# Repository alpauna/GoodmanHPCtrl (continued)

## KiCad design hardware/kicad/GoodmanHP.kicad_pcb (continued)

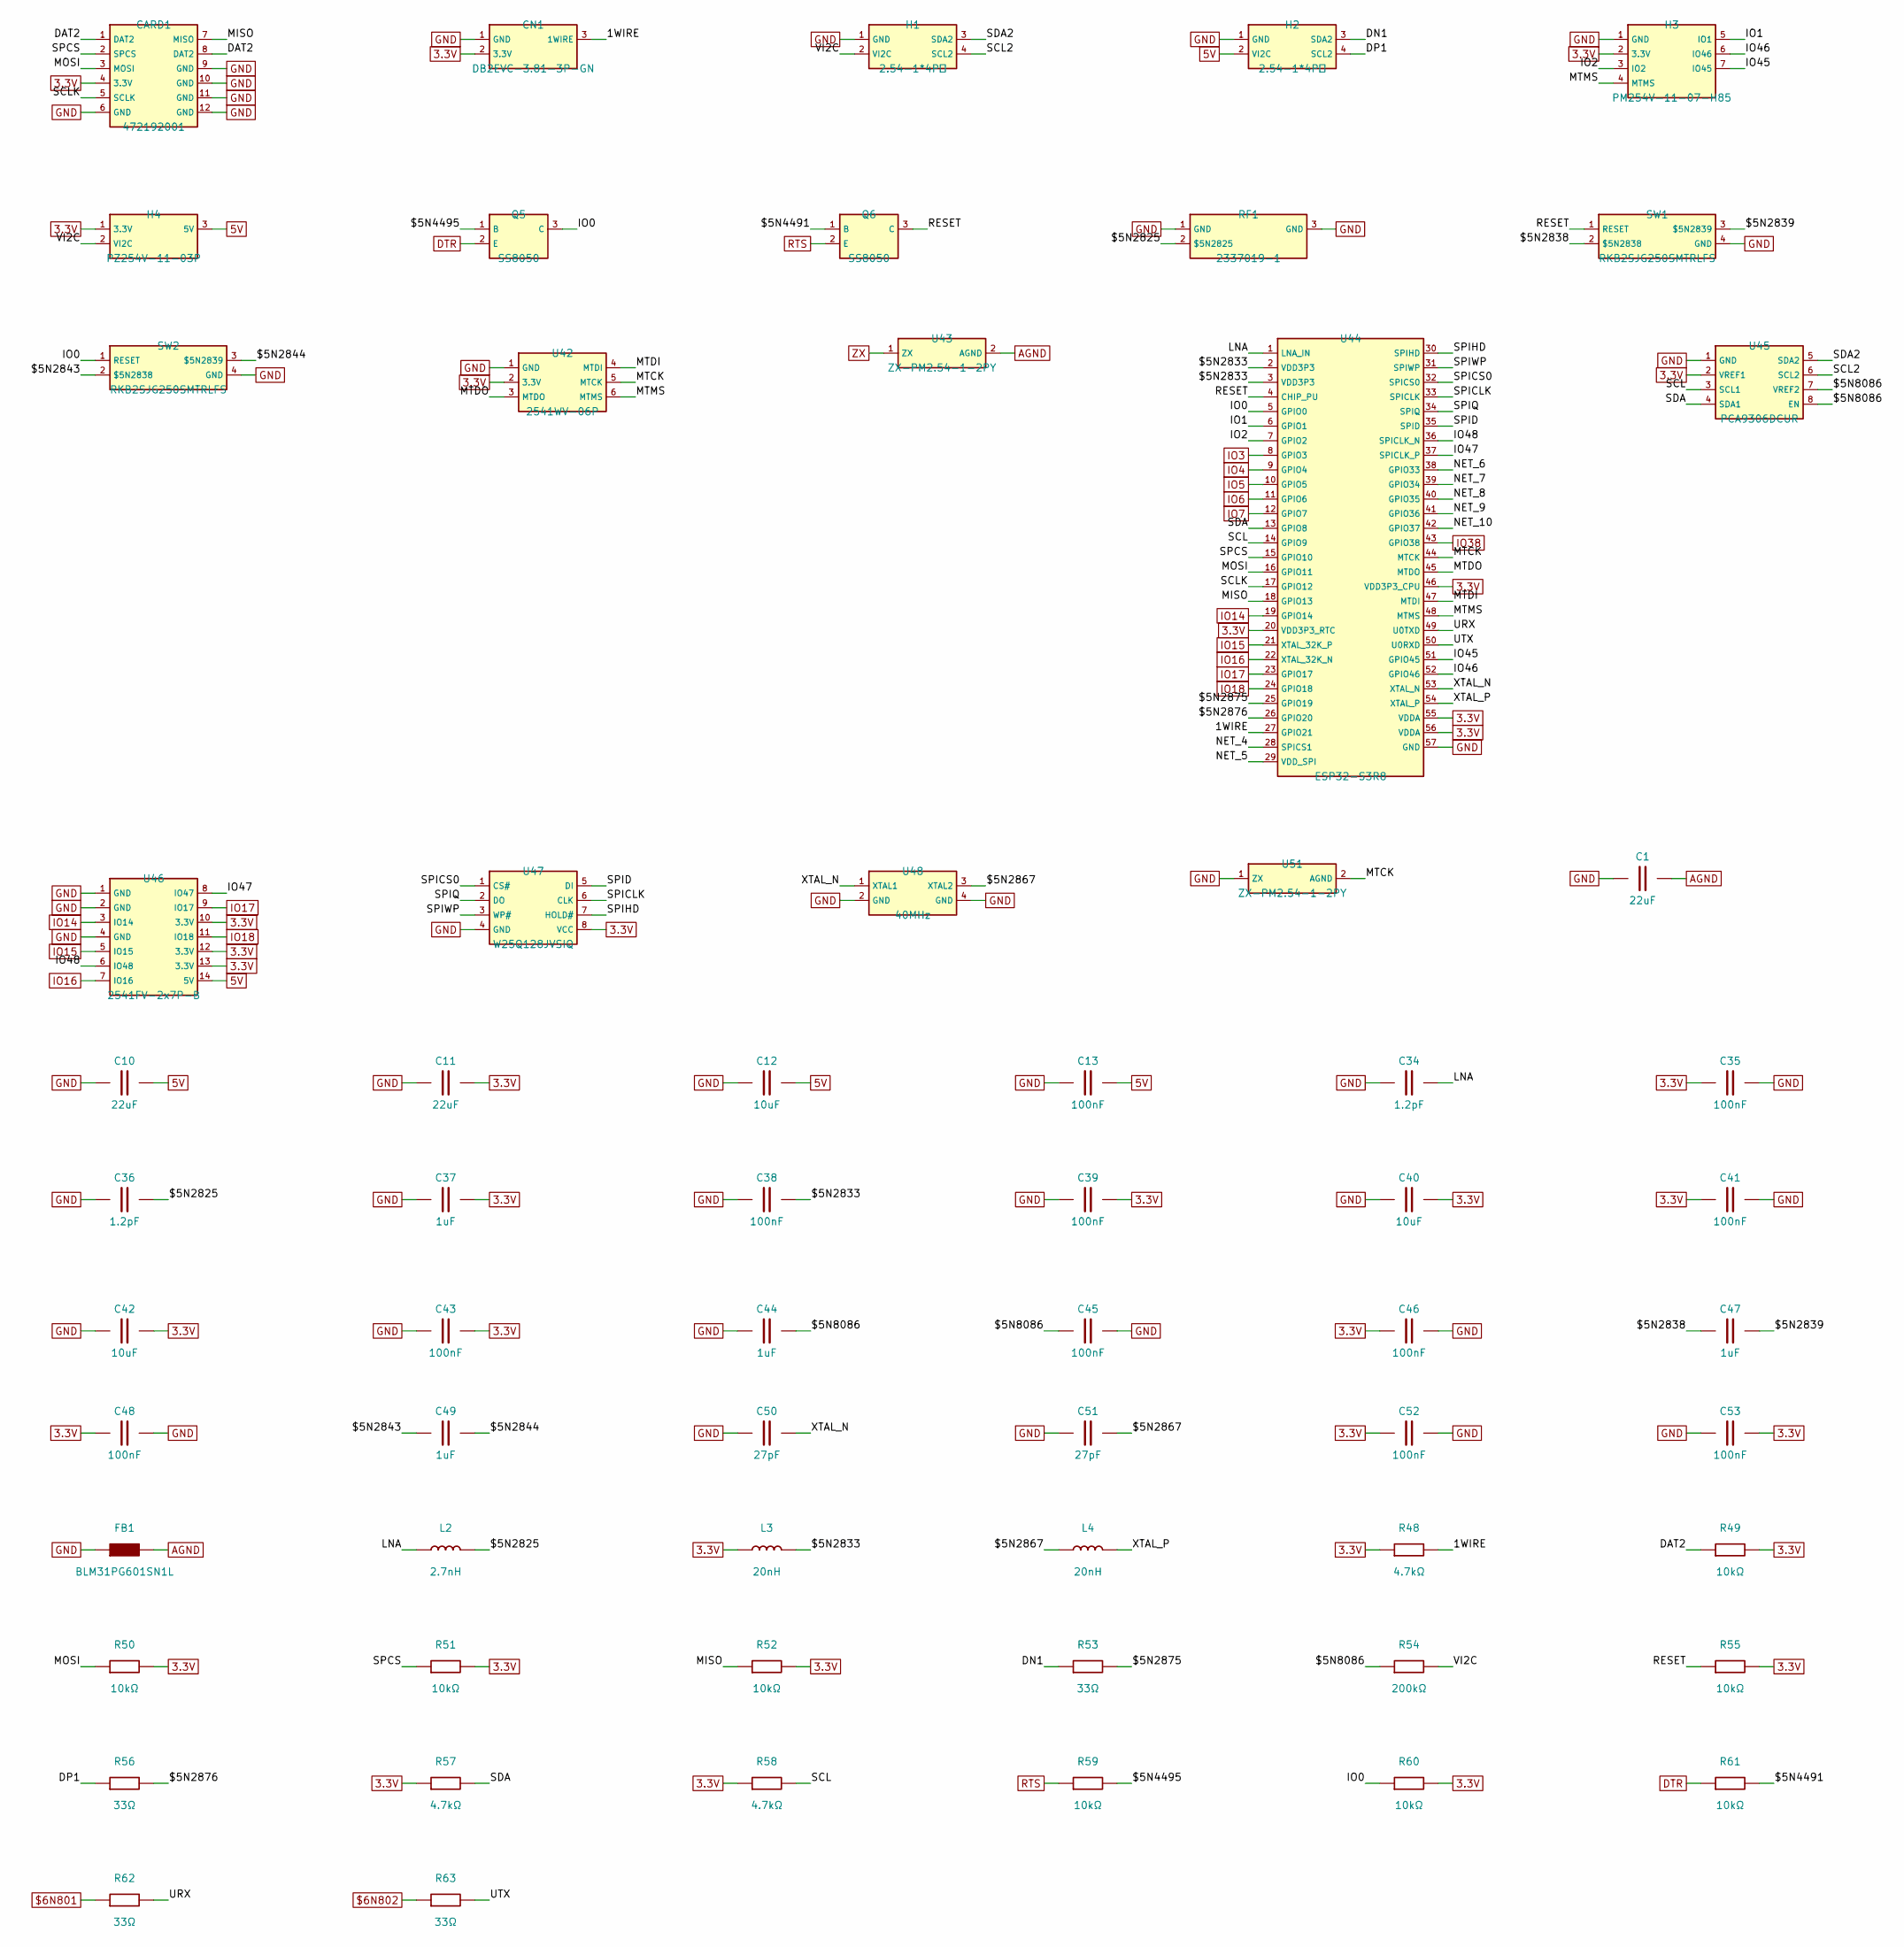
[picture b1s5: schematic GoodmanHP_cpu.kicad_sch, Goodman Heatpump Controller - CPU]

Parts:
C1: 22uF; C1812; LCSC C22388553
C10, C11: 22uF; C0805; LCSC C907991
C12, C40, C42: 10uF; C0402; LCSC C15525
C13, C35, C38, C39, C41, C43, C45, C46, C48, C52, C53: 100nF; C0201; LCSC C85923
C34, C36: 1.2pF; C0201; LCSC C85895
C37, C44, C47, C49: 1uF; C0201; LCSC C76929
C50, C51: 27pF; C0201; LCSC C384976
CARD1: 472192001; TF-SMD_472192001; LCSC C164170
CN1: DB2EVC-3.81-3P-GN; CONN-TH_3P-P3.81_DB2EVC-3.81-3P; LCSC C395692
FB1: BLM31PG601SN1L; L1206; LCSC C16902
H1, H2: 2.54-1*4P母; HDR-TH_4P-P2.54-V-F; LCSC C2718488
H3: PM254V-11-07-H85; HDR-TH_7P-P2.54-V-F; LCSC C2832270
H4: PZ254V-11-03P; HDR-TH_3P-P2.54-V-M_PZ254V-11-03P; LCSC C2937625
L2: 2.7nH; L0201; LCSC C7216765
L3, L4: 20nH; IND-SMD_L1.2-W0.6-1; LCSC C330860
Q5, Q6: SS8050; SOT-23-3_L2.9-W1.3-P1.90-LS2.4-BR; LCSC C916392
R48, R57, R58: 4.7kΩ; R0201; LCSC C138135
R49, R50, R51, R52, R55, R59, R60, R61: 10kΩ; R0201; LCSC C473048
R53, R56, R62, R63: 33Ω; R0201; LCSC C423356
R54: 200kΩ; R0201; LCSC C138163
RF1: 2337019-1; ANT-SMD_2337019-1; LCSC C434807
SW1, SW2: RKB2SJG250SMTRLFS; SW-SMD_4P-L4.2-W3.2-P2.15-LS4.6; LCSC C2927788
U42: 2541WV-06P; HDR-TH_6P-P2.54-V-M; LCSC C5383115
U43, U51: ZX-PM2.54-1-2PY; HDR-TH_2P-P2.54-V-F; LCSC C7499322
U44: ESP32-S3R8; QFN-56_L7.0-W7.0-P0.40-TL-EP4.0; LCSC C2913194
U45: PCA9306DCUR; SSOP-8_L2.0-W2.3-P0.50-LS3.1-BR; LCSC C33196
U46: 2541FV-2x7P-B; HDR-TH_2541FV-2X7P-B; LCSC C25503125
U47: W25Q128JVSIQ; SOIC-8_L5.3-W5.3-P1.27-LS8.0-BL; LCSC C113767
U48: 40MHz; CRYSTAL-SMD_4P-L2.0-W1.6-BL; LCSC C42464327

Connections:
1WIRE: CN1.3 (1WIRE), R48.2, U44.27 (GPIO21)
3.3V: C11.2, C35.1, C37.2, C39.2, C40.2, C41.1, C42.2, C43.2, C46.1, C48.1, C52.1, C53.2, CARD1.4 (3.3V), CN1.2 (3.3V), H3.2 (3.3V), H4.1 (3.3V), L3.1, R48.1, R49.2, R50.2, R51.2, R52.2, R55.2, R57.1, R58.1, R60.2, U42.2 (3.3V), U44.20 (VDD3P3_RTC), U44.46 (VDD3P3_CPU), U44.55 (VDDA), U44.56 (VDDA), U45.2 (VREF1), U46.10 (3.3V), U46.12 (3.3V), U46.13 (3.3V), U47.8 (VCC); also elsewhere on the board
5V: C10.2, C12.2, C13.2, H2.2 (VI2C), H4.3 (5V), U46.14 (5V); also elsewhere on the board
$5N2825: C36.2, L2.2, RF1.2 ($5N2825)
$5N2833: C38.2, L3.2, U44.2 (VDD3P3), U44.3 (VDD3P3)
$5N2838: C47.1, SW1.2 ($5N2838)
$5N2839: C47.2, SW1.3 ($5N2839)
$5N2843: C49.1, SW2.2 ($5N2838)
$5N2844: C49.2, SW2.3 ($5N2839)
$5N2867: C51.2, L4.1, U48.3 (XTAL2)
$5N2875: R53.2, U44.25 (GPIO19)
$5N2876: R56.2, U44.26 (GPIO20)
$5N4491: Q6.1 (B), R61.2
$5N4495: Q5.1 (B), R59.2
$5N8086: C44.2, C45.1, R54.1, U45.7 (VREF2), U45.8 (EN)
$6N801: R62.1; also elsewhere on the board
$6N802: R63.1; also elsewhere on the board
AGND: C1.2, FB1.2, U43.2 (AGND); also elsewhere on the board
DAT2: CARD1.1 (DAT2), CARD1.8 (DAT2), R49.1
DN1: H2.3 (SDA2), R53.1
DP1: H2.4 (SCL2), R56.1
DTR: Q5.2 (E), R61.1; also elsewhere on the board
GND: C1.1, C10.1, C11.1, C12.1, C13.1, C34.1, C35.2, C36.1, C37.1, C38.1, C39.1, C40.1, C41.2, C42.1, C43.1, C44.1, C45.2, C46.2, C48.2, C50.1, C51.1, C52.2, C53.1, CARD1.6 (GND), CARD1.9 (GND), CARD1.10 (GND), CARD1.11 (GND), CARD1.12 (GND), CN1.1 (GND), FB1.1, H1.1 (GND), H2.1 (GND), H3.1 (GND), RF1.1 (GND), RF1.3 (GND), SW1.4 (GND), SW2.4 (GND), U42.1 (GND), U44.57 (GND), U45.1 (GND), U46.1 (GND), U46.2 (GND), U46.4 (GND), U47.4 (GND), U48.2 (GND), U48.4 (GND), U51.1 (ZX); also elsewhere on the board
IO0: Q5.3 (C), R60.1, SW2.1 (RESET), U44.5 (GPIO0)
IO1: H3.5 (IO1), U44.6 (GPIO1)
IO2: H3.3 (IO2), U44.7 (GPIO2)
IO3: U44.8 (GPIO3); also elsewhere on the board
IO4: U44.9 (GPIO4); also elsewhere on the board
IO5: U44.10 (GPIO5); also elsewhere on the board
IO6: U44.11 (GPIO6); also elsewhere on the board
IO7: U44.12 (GPIO7); also elsewhere on the board
IO14: U44.19 (GPIO14), U46.3 (IO14); also elsewhere on the board
IO15: U44.21 (XTAL_32K_P), U46.5 (IO15); also elsewhere on the board
IO16: U44.22 (XTAL_32K_N), U46.7 (IO16); also elsewhere on the board
IO17: U44.23 (GPIO17), U46.9 (IO17); also elsewhere on the board
IO18: U44.24 (GPIO18), U46.11 (IO18); also elsewhere on the board
IO38: U44.43 (GPIO38); also elsewhere on the board
IO45: H3.7 (IO45), U44.51 (GPIO45)
IO46: H3.6 (IO46), U44.52 (GPIO46)
IO47: U44.37 (SPICLK_P), U46.8 (IO47)
IO48: U44.36 (SPICLK_N), U46.6 (IO48)
LNA: C34.2, L2.1, U44.1 (LNA_IN)
MISO: CARD1.7 (MISO), R52.1, U44.18 (GPIO13)
MOSI: CARD1.3 (MOSI), R50.1, U44.16 (GPIO11)
MTCK: U42.5 (MTCK), U44.44 (MTCK), U51.2 (AGND)
MTDI: U42.4 (MTDI), U44.47 (MTDI)
MTDO: U42.3 (MTDO), U44.45 (MTDO)
MTMS: H3.4 (MTMS), U42.6 (MTMS), U44.48 (MTMS)
NET_4: U44.28 (SPICS1)
NET_5: U44.29 (VDD_SPI)
NET_6: U44.38 (GPIO33)
NET_7: U44.39 (GPIO34)
NET_8: U44.40 (GPIO35)
NET_9: U44.41 (GPIO36)
NET_10: U44.42 (GPIO37)
RESET: Q6.3 (C), R55.1, SW1.1 (RESET), U44.4 (CHIP_PU)
RTS: Q6.2 (E), R59.1; also elsewhere on the board
SCL: R58.2, U44.14 (GPIO9), U45.3 (SCL1)
SCL2: H1.4 (SCL2), U45.6 (SCL2)
SCLK: CARD1.5 (SCLK), U44.17 (GPIO12)
SDA: R57.2, U44.13 (GPIO8), U45.4 (SDA1)
SDA2: H1.3 (SDA2), U45.5 (SDA2)
SPCS: CARD1.2 (SPCS), R51.1, U44.15 (GPIO10)
SPICLK: U44.33 (SPICLK), U47.6 (CLK)
SPICS0: U44.32 (SPICS0), U47.1 (CS#)
SPID: U44.35 (SPID), U47.5 (DI)
SPIHD: U44.30 (SPIHD), U47.7 (HOLD#)
SPIQ: U44.34 (SPIQ), U47.2 (DO)
SPIWP: U44.31 (SPIWP), U47.3 (WP#)
URX: R62.2, U44.49 (U0TXD)
UTX: R63.2, U44.50 (U0RXD)
VI2C: H1.2 (VI2C), H4.2 (VI2C), R54.2
XTAL_N: C50.2, U44.53 (XTAL_N), U48.1 (XTAL1)
XTAL_P: L4.2, U44.54 (XTAL_P)
ZX: U43.1 (ZX); also elsewhere on the board

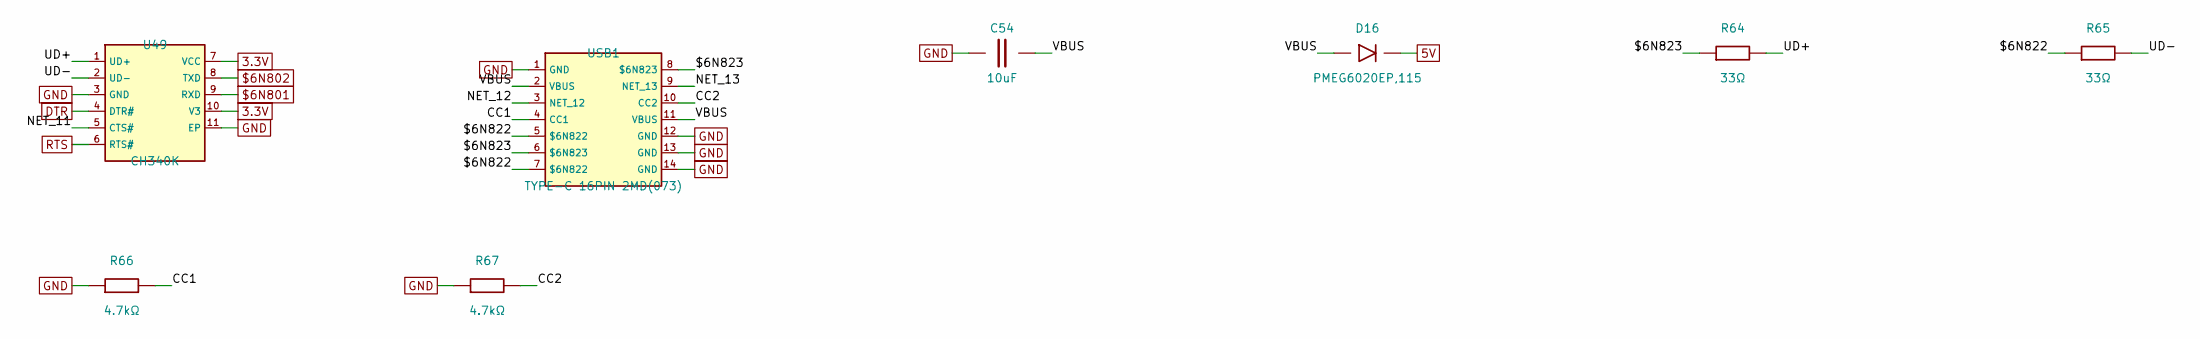
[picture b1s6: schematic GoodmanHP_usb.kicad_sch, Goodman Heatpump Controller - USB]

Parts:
C54: 10uF; C0402; LCSC C15525
D16: PMEG6020EP,115; SOD-128_L3.7-W2.5-LS4.7-FD; LCSC C179433
R64, R65: 33Ω; R0201; LCSC C423356
R66, R67: 4.7kΩ; R0201; LCSC C138135
U49: CH340K; ESOP-10_L4.9-W3.9-P1.00-LS6.2-BL-EP; LCSC C968586
USB1: TYPE-C 16PIN 2MD(073); USB-C-SMD_TYPE-C-6PIN-2MD-073; LCSC C2765186

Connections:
3.3V: U49.7 (VCC), U49.10 (V3); also elsewhere on the board
5V: D16.1 (K); also elsewhere on the board
$6N801: U49.9 (RXD); also elsewhere on the board
$6N802: U49.8 (TXD); also elsewhere on the board
$6N822: R65.1, USB1.5 ($6N822), USB1.7 ($6N822)
$6N823: R64.1, USB1.6 ($6N823), USB1.8 ($6N823)
CC1: R66.2, USB1.4 (CC1)
CC2: R67.2, USB1.10 (CC2)
DTR: U49.4 (DTR#); also elsewhere on the board
GND: C54.1, R66.1, R67.1, U49.3 (GND), U49.11 (EP), USB1.1 (GND), USB1.12 (GND), USB1.13 (GND), USB1.14 (GND); also elsewhere on the board
NET_11: U49.5 (CTS#)
NET_12: USB1.3 (NET_12)
NET_13: USB1.9 (NET_13)
RTS: U49.6 (RTS#); also elsewhere on the board
UD+: R64.2, U49.1 (UD+)
UD-: R65.2, U49.2 (UD-)
VBUS: C54.2, D16.2 (A), USB1.2 (VBUS), USB1.11 (VBUS)

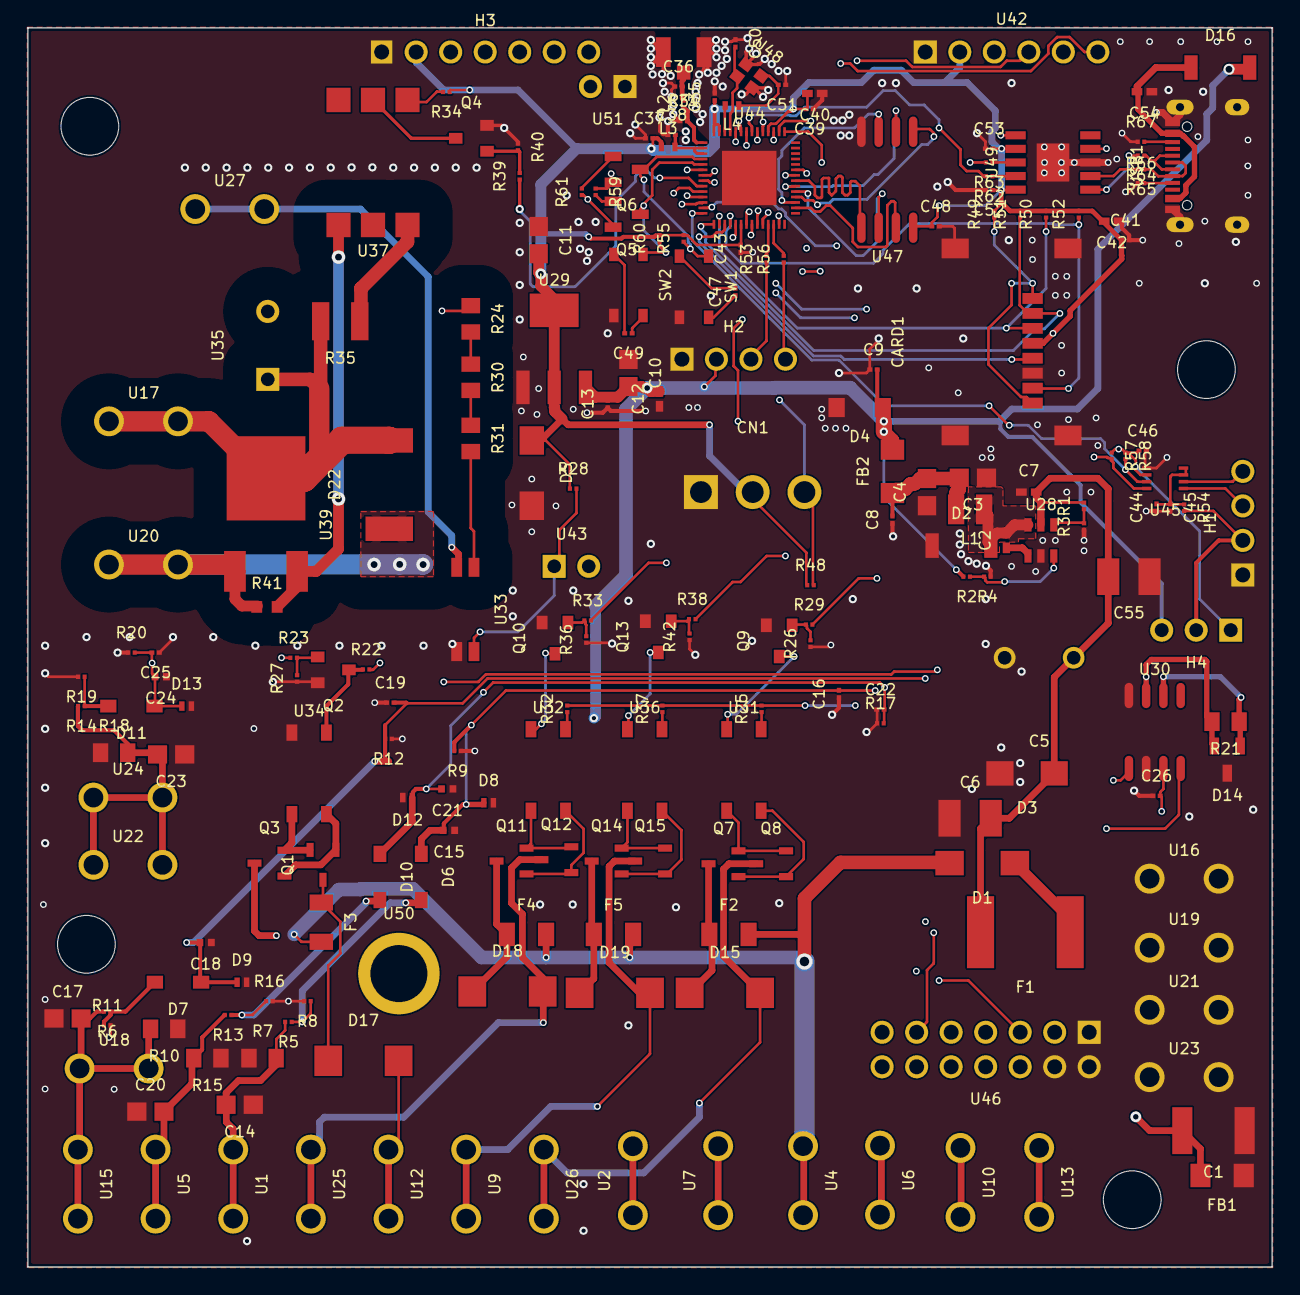
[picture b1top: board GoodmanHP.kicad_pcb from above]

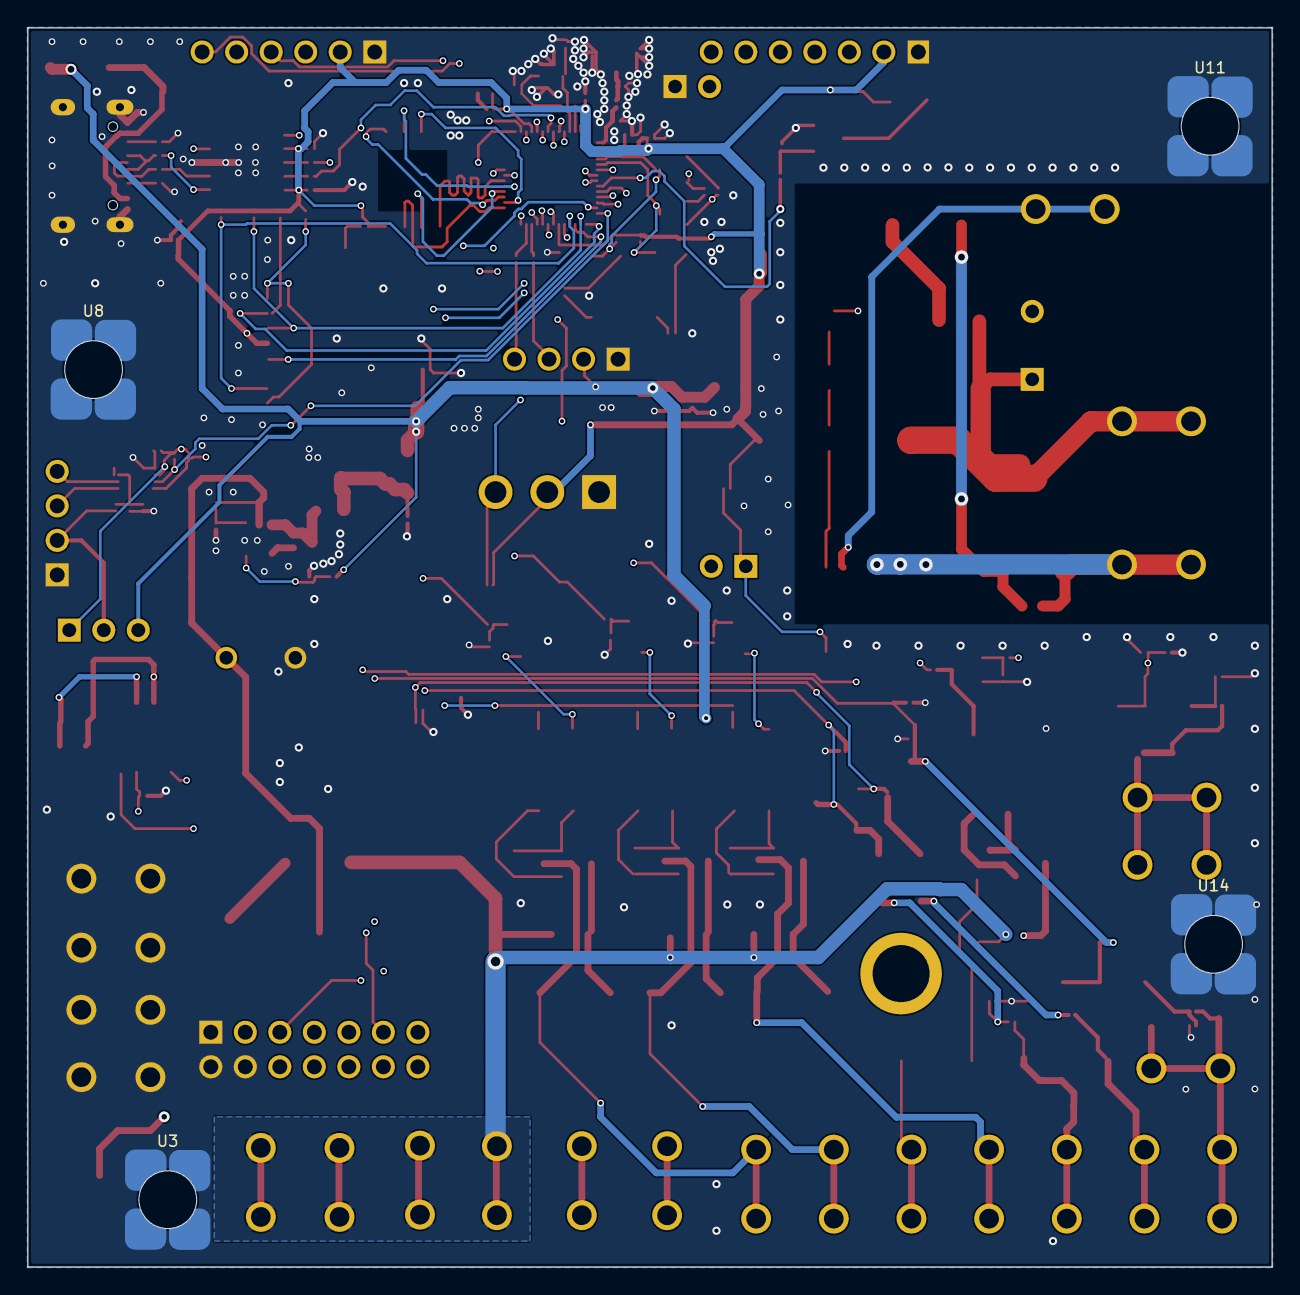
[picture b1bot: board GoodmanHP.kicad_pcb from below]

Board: 6 copper layers, 91.6 x 91.2 mm, 220 parts (4 on the bottom side), 132 nets.

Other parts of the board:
MH1, MH2, MH3, MH4, MH5, MH6: (no value)

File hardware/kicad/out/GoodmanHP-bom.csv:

"Reference","Value","Footprint","LCSC","Manufacturer","QUANTITY"
"C1","22uF","GoodmanHP:C1812","C22388553","PSA(信昌电陶)","1"
"C2,C7","100nF","GoodmanHP:C0402","C77020","muRata(村田)","2"
"C3,C4,C10,C11","22uF","GoodmanHP:C0805","C907991","muRata(村田)","4"
"C5","560uF","GoodmanHP:CAP-TH_BD10.0-P5.00-D1.0-FD_1","C49309240","KNSCHA(科尼盛)","1"
"C6,C55","10uF","GoodmanHP:C1210","C437568","muRata(村田)","2"
"C8,C9,C37,C44,C47,C49","1uF","GoodmanHP:C0201","C76929","muRata(村田)","6"
"C12,C40,C42,C54","10uF","GoodmanHP:C0402","C15525","SAMSUNG(三星)","4"
"C13,C16,C19,C22,C25,C26,C35,C38,C39,C41,C43,C45,C46,C48,C52,C53","100nF","GoodmanHP:C0201","C85923","muRata(村田)","16"
"C14,C17,C20,C23","2.2uF","GoodmanHP:C0805","C22367838","Chinocera(华瓷)","4"
"C15,C18,C21,C24","4.7uF","GoodmanHP:C0402","C20624278","FH(风华)","4"
"C34,C36","1.2pF","GoodmanHP:C0201","C85895","muRata(村田)","2"
"C50,C51","27pF","GoodmanHP:C0201","C384976","muRata","2"
"CARD1","472192001","GoodmanHP:TF-SMD_472192001","C164170","MOLEX","1"
"CN1","DB2EVC-3.81-3P-GN","GoodmanHP:CONN-TH_3P-P3.81_DB2EVC-3.81-3P","C395692","DORABO(地博电气)","1"
"D1","RS2M","GoodmanHP:SMA_L4.3-W2.7-LS5.1-RD","C908426","GOODWORK(固得沃克)","1"
"D2,D16","PMEG6020EP,115","GoodmanHP:SOD-128_L3.7-W2.5-LS4.7-FD","C179433","Nexperia(安世)","2"
"D3","SMAJ36CA","GoodmanHP:SMA_L4.2-W2.7-LS5.0-BI","C908830","GOODWORK(固得沃克)","1"
"D4","SMF5.0A","GoodmanHP:SOD-123FL_L2.8-W1.9-LS3.7-RD","C2857263","JSMSEMI(杰盛微)","1"
"D5","SMAJ3.3A","GoodmanHP:SMA_L4.3-W2.7-LS5.1-RD","C22365220","DOWO(东沃)","1"
"D6,D7,D10,D11","1N4148W-7-F","GoodmanHP:SOD-123_L2.7-W1.6-LS3.7-RD-1","C83528","DIODES(美台)","4"
"D8,D9,D12,D13","BZX884-B3V3,315","GoodmanHP:SOD-882_L1.0-W0.6-RD","C551199","Nexperia(安世)","4"
"D14","ESDCAN24-2BLY","GoodmanHP:SOT-23-3_L2.9-W1.3-P1.90-LS2.4-BL-2","C2937021","TECH PUBLIC","1"
"D15,D17-D19","TPSMB47CA","GoodmanHP:SMB_L4.3-W3.6-LS5.4-BI","C1975322","Littelfuse(美国力特)","4"
"D22","SMCJ400CA","GoodmanHP:SMCG_L6.8-W5.8-LS7.9-BI","C5294118","CJ(江苏长电/长晶)","1"
"F1","2920L050/90GR","GoodmanHP:F2920","C41414044","LUTE(陆特)","1"
"F2-F5","1206L025/60NR","GoodmanHP:F1206","C47345582","LUTE(陆特)","4"
"FB1,FB2","BLM31PG601SN1L","GoodmanHP:L1206","C16902","muRata(村田)","2"
"H1,H2","2.54-1*4P母","GoodmanHP:HDR-TH_4P-P2.54-V-F","C2718488","BOOMELE(博穆精密)","2"
"H3","PM254V-11-07-H85","GoodmanHP:HDR-TH_7P-P2.54-V-F","C2832270","XFCN(兴飞)","1"
"H4","PZ254V-11-03P","GoodmanHP:HDR-TH_3P-P2.54-V-M_PZ254V-11-03P","C2937625","XFCN(兴飞)","1"
"L1","10uH","GoodmanHP:IND-SMD_L2.5-W2.0","C5832376","cjiang(长江微电)","1"
"L2","2.7nH","GoodmanHP:L0201","C7216765","muRata(村田)","1"
"L3,L4","20nH","GoodmanHP:IND-SMD_L1.2-W0.6-1","C330860","Sunltech(顺磁)","2"
"Q1,Q3,Q7,Q8,Q11,Q12,Q14,Q15","HSS2N12A","GoodmanHP:SOT-23-3_L3.0-W1.7-P0.95-LS2.9-BR","C53243986","HUASHUO(华朔)","8"
"Q2,Q4,Q9,Q10,Q13","L2N7002LT1G","GoodmanHP:SOT-23_L2.9-W1.3-P1.90-LS2.4-BR","C12779","LRC(乐山无线电)","5"
"Q5,Q6","SS8050","GoodmanHP:SOT-23-3_L2.9-W1.3-P1.90-LS2.4-BR","C916392","JSMSEMI(杰盛微)","2"
"R1,R5,R6,R13,R14,R28","33kΩ","GoodmanHP:R0201","C473534","UNI-ROYAL(厚声)","6"
"R2","9.31kΩ","GoodmanHP:R0201","C423401","UNI-ROYAL(厚声)","1"
"R3","2kΩ","GoodmanHP:R0201","C851709","YAGEO(国巨)","1"
"R4","1.8kΩ","GoodmanHP:R0201","C473568","UNI-ROYAL(厚声)","1"
"R7,R10,R15,R18","5.6kΩ","GoodmanHP:R0805","C441985","PANASONIC(松下)","4"
"R8,R11,R16,R19,R26,R27,R36,R40,R42,R49-R52,R55,R59-R61","10kΩ","GoodmanHP:R0201","C473048","UNI-ROYAL(厚声)","17"
"R9,R12,R17,R20","1MΩ","GoodmanHP:R0201","C295786","YAGEO(国巨)","4"
"R21","120Ω","GoodmanHP:R0805","C844392","VISHAY(威世)","1"
"R22,R23,R25,R29,R32,R33,R37-R39","180Ω","GoodmanHP:R0201","C965335","UNI-ROYAL(厚声)","9"
"R24,R30,R31","100kΩ","GoodmanHP:R0805_NEW","C96346","YAGEO(国巨)","3"
"R34","100Ω","GoodmanHP:R0201","C77623","YAGEO(国巨)","1"
"R35","390Ω","GoodmanHP:R1210","C2960731","FOJAN(富捷)","1"
"R41","10kΩ","GoodmanHP:R0603","C2906982","FOJAN(富捷)","1"
"R48,R57,R58,R66,R67","4.7kΩ","GoodmanHP:R0201","C138135","YAGEO(国巨)","5"
"R53,R56,R62-R65","33Ω","GoodmanHP:R0201","C423356","UNI-ROYAL(厚声)","6"
"R54","200kΩ","GoodmanHP:R0201","C138163","YAGEO(国巨)","1"
"RF1","2337019-1","GoodmanHP:ANT-SMD_2337019-1","C434807","TE Connectivity(泰科电子)","1"
"SW1,SW2","RKB2SJG250SMTRLFS","GoodmanHP:SW-SMD_4P-L4.2-W3.2-P2.15-LS4.6","C2927788","C&K","2"
"U1,U2,U4-U7,U9,U10,U12,U13,U15-U27","1217861-1 Faston","GoodmanHP:1217861-1","C428480","","23"
"U3,U8,U11,U14","SMTSO3280CTJ","GoodmanHP:SMD_BD5.6-L5.6-W5.6-D4.1","C2928174","Sinhoo(雄和远景)","4"
"U28","LGS5145","GoodmanHP:SOT-23-6_L2.9-W1.7-P0.95-LS2.8-BL","C5123971","Legend-Si(棱晶半导体)","1"
"U29","TLV76133DCYR","GoodmanHP:SOT-223-4_L6.5-W3.5-P2.30-LS7.0-TR","C7527500","TI(德州仪器)","1"
"U30","SN65HVD230DR-JSM","GoodmanHP:SOP-8_L4.9-W3.9-P1.27-LS6.0-BL","C46596299","JSMSEMI(杰盛微)","1"
"U31,U32,U34,U36","GAQV1122S","GoodmanHP:SOP-4_L4.3-W4.4-P2.54-LS6.8-TR","C22385006","SUPSiC(国晶微半导体)","4"
"U33","AT3H4B-CuH-S","GoodmanHP:SSOP-4_L2.7-W4.6-P1.27-LS7.0-TL","C20612635","AOTE(奥特)","1"
"U35","B59850C0130A070","GoodmanHP:RES-TH_L11.0-W5.0-P5.00-D0.8","C125471","TDK","1"
"U37","MOC3041SM","GoodmanHP:SMD-6_L8.8-W6.4-P2.54-LS9.4-BL","C22373366","AOTE(奥特)","1"
"U39","BT138S-800E","GoodmanHP:TO-252-2_L6.6-W6.1-P4.57-LS10.1-BR-CW","C5380690","FUXINSEMI(富芯森美)","1"
"U42","2541WV-06P","GoodmanHP:HDR-TH_6P-P2.54-V-M","C5383115","HanElectricity(瀚源)","1"
"U43,U51","ZX-PM2.54-1-2PY","GoodmanHP:HDR-TH_2P-P2.54-V-F","C7499322","Megastar(兆星)","2"
"U44","ESP32-S3R8","GoodmanHP:QFN-56_L7.0-W7.0-P0.40-TL-EP4.0","C2913194","ESPRESSIF(乐鑫)","1"
"U45","PCA9306DCUR","GoodmanHP:SSOP-8_L2.0-W2.3-P0.50-LS3.1-BR","C33196","TI(德州仪器)","1"
"U46","2541FV-2x7P-B","GoodmanHP:HDR-TH_2541FV-2X7P-B","C25503125","HanElectricity(瀚源)","1"
"U47","W25Q128JVSIQ","GoodmanHP:SOIC-8_L5.3-W5.3-P1.27-LS8.0-BL","C113767","Winbond(华邦)","1"
"U48","40MHz","GoodmanHP:CRYSTAL-SMD_4P-L2.0-W1.6-BL","C42464327","TOGNJING","1"
"U49","CH340K","GoodmanHP:ESOP-10_L4.9-W3.9-P1.00-LS6.2-BL-EP","C968586","WCH(南京沁恒)","1"
"U50","SMTSO30100CTJ","GoodmanHP:SCREW-SMD_BD5.6-D4.1-H10","C2916370","Sinhoo(雄和远景)","1"
"USB1","TYPE-C 16PIN 2MD(073)","GoodmanHP:USB-C-SMD_TYPE-C-6PIN-2MD-073","C2765186","SHOU HAN(首韩)","1"

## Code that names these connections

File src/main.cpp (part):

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// proven live via bringup/ads131m04/main.cpp -- see
// docs/ads131m04-current-sensor-design.md "Main-board interconnect".
// GPIO39 (RESET#/SYNC#) is a hand-soldered bodge wire onto the main board's
// JTAG debug header (MTCK), not a proper H3 connector pin -- H3 is a fixed
// 7-position part on the already-fabricated board with no 8th conductor
// available. See "RESET# bodge wire" / "Next PCB revision requirements" in
// the design doc.
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
  if (!_safeMode) {
    // Add input pins to GoodmanHP controller
    hpController.addInput("LPS", new InputPin(&ts, proj.inputDelayMs, InputResistorType::IT_PULLDOWN, InputPinType::IT_DIGITAL, _lpsPin, "LPS", "LPS", onInput));
    hpController.addInput("DFT", new InputPin(&ts, proj.inputDelayMs, InputResistorType::IT_PULLDOWN, InputPinType::IT_DIGITAL, _dftPin, "DFT", "DFT", onInput));
    hpController.addInput("Y", new InputPin(&ts, proj.inputDelayMs, InputResistorType::NONE, InputPinType::IT_DIGITAL, _yPin, "Y", "OT-NO", onInput));
    hpController.addInput("O", new InputPin(&ts, proj.inputDelayMs, InputResistorType::IT_PULLDOWN, InputPinType::IT_DIGITAL, _oPin, "O", "OT-NC", onInput));

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
    // Add output pins to GoodmanHP controller (initPin drives GPIO LOW)
    hpController.addOutput("FAN", new OutPin(&ts, 0, _fanPin, "FAN", "FAN", onOutpin));
    hpController.addOutput("CNT", new OutPin(&ts, 3000, _CNTPin, "CNT", "CNT", onOutpin));
    hpController.addOutput("W", new OutPin(&ts, 0, _WPin, "W", "W", onOutpin));
    hpController.addOutput("RV", new OutPin(&ts, 0, _RVPin, "RV", "RV", onOutpin));
    // AUX/LT is normally-closed at the hardware level (Q1 shunts the opto LED to
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
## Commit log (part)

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2026-02-06 Cleaned up main.cpp
2026-02-06 Cleaned up input and output pins callbacks on main.cpp
2026-02-07 Updated and cleaned up some main.ccp and Outpin added to check actual pin state.
